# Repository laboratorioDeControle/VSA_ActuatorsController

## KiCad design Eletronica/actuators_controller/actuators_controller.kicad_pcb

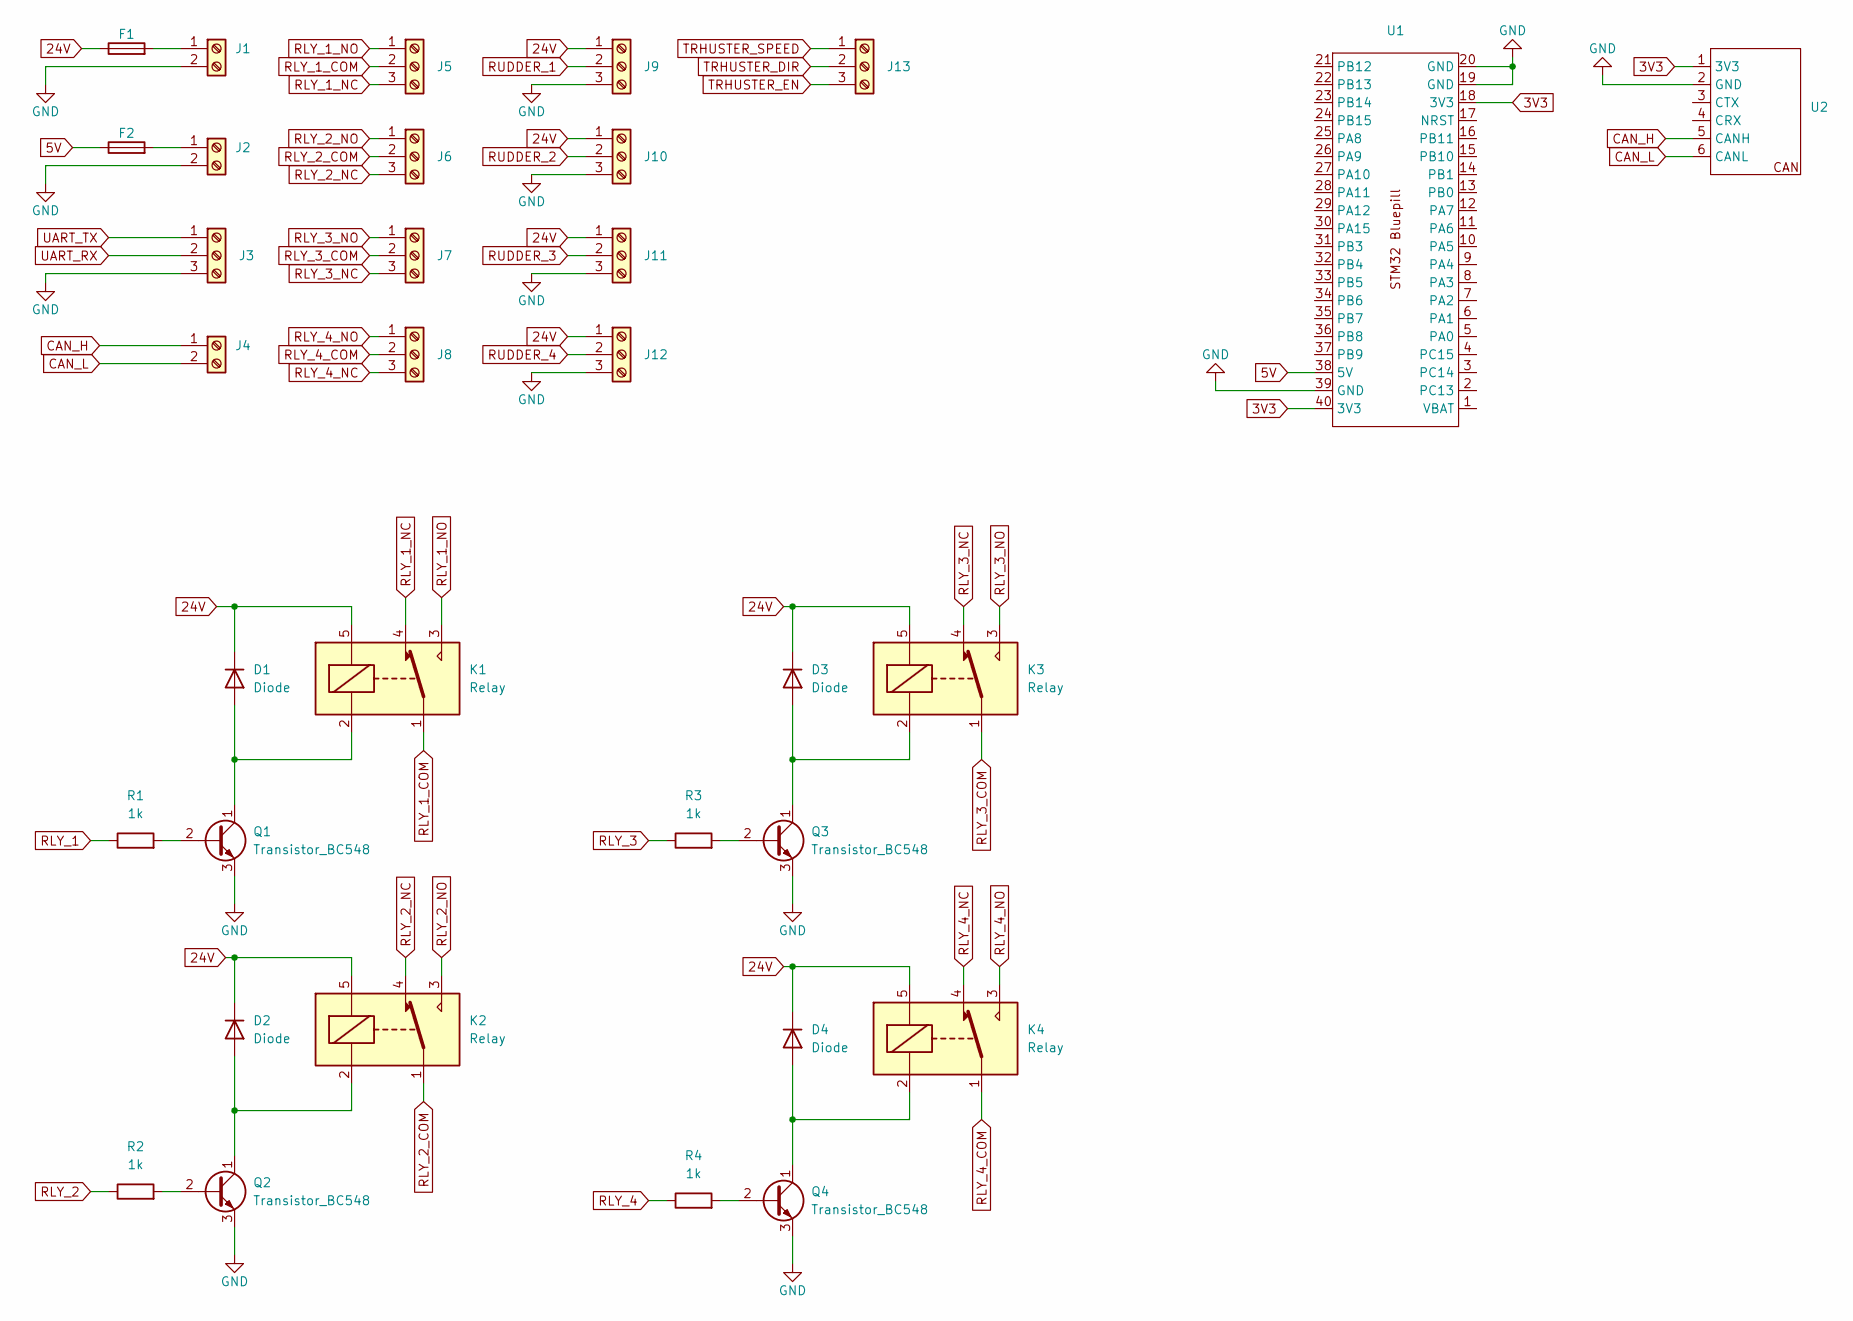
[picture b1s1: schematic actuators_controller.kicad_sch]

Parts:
D1, D2, D3, D4: Diode; D_DO-41_SOD81_P10.16mm_Horizontal
F1, F2: Fuse; Fuse_Blade_Mini_directSolder
J1, J2, J4: Screw_Terminal_01x02; Borne_2EDGR_2Pins_5.08mm_BigPadds
J3, J5, J6, J7, J8, J9, J10, J11, J12, J13: Screw_Terminal_01x03; Borne_2EDGR_3Pins_5.08mm_BigPadds
K1, K2, K3, K4: Relay; Relay_BigPadds
Q1, Q2, Q3, Q4: Transistor_BC548
R1, R2, R3, R4: 1k; Resistor_BigPadds
U1: STM32_Bluepill_PTH_BigPadds
U2: (no value)

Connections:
3V3: U1.18 (3V3), U1.40 (3V3), U2.1 (3V3)
5V: F2.1, U1.38 (5V)
24V: D1.1 (K), D2.1 (K), D3.1 (K), D4.1 (K), F1.1, J9.1, J10.1, J11.1, J12.1, K1.5, K2.5, K3.5, K4.5
CAN_H: J4.1, U2.5 (CANH)
CAN_L: J4.2, U2.6 (CANL)
GND: J1.2, J2.2, J3.3, J9.3, J10.3, J11.3, J12.3, Q1.3 (E), Q2.3 (E), Q3.3 (E), Q4.3 (E), U1.19 (GND), U1.20 (GND), U1.39 (GND), U2.2 (GND)
unnamed: D1.2 (A), K1.2, Q1.1 (C)
unnamed: D2.2 (A), K2.2, Q2.1 (C)
unnamed: D3.2 (A), K3.2, Q3.1 (C)
unnamed: D4.2 (A), K4.2, Q4.1 (C)
unnamed: F1.2, J1.1
unnamed: F2.2, J2.1
unnamed: Q1.2 (B), R1.2
unnamed: Q2.2 (B), R2.2
unnamed: Q3.2 (B), R3.2
unnamed: Q4.2 (B), R4.2
RLY_1: R1.1
RLY_1_COM: J5.2, K1.1
RLY_1_NC: J5.3, K1.4
RLY_1_NO: J5.1, K1.3
RLY_2: R2.1
RLY_2_COM: J6.2, K2.1
RLY_2_NC: J6.3, K2.4
RLY_2_NO: J6.1, K2.3
RLY_3: R3.1
RLY_3_COM: J7.2, K3.1
RLY_3_NC: J7.3, K3.4
RLY_3_NO: J7.1, K3.3
RLY_4: R4.1
RLY_4_COM: J8.2, K4.1
RLY_4_NC: J8.3, K4.4
RLY_4_NO: J8.1, K4.3
RUDDER_1: J9.2
RUDDER_2: J10.2
RUDDER_3: J11.2
RUDDER_4: J12.2
TRHUSTER_DIR: J13.2
TRHUSTER_EN: J13.3
TRHUSTER_SPEED: J13.1
UART_RX: J3.2
UART_TX: J3.1

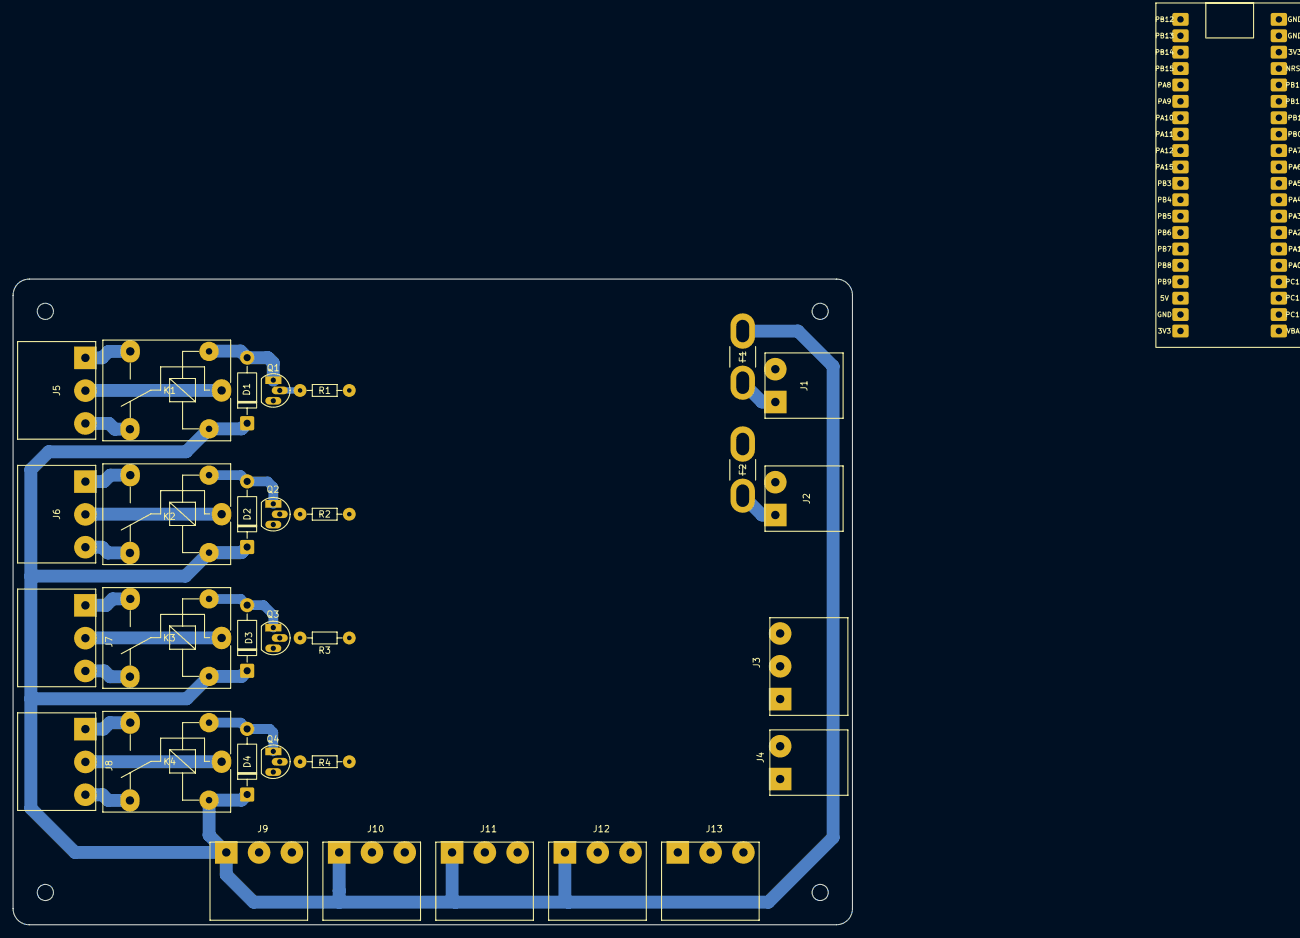
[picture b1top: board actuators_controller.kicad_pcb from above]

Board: 2 copper layers, 130.0 x 100.0 mm, 32 parts (0 on the bottom side), 26 nets.
